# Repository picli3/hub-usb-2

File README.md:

# hub-usb-2

Hub USB 2.0 desarrollado en KiCad, pensado para distribuir conectividad USB desde una placa propia con regulación y protección integradas.

## Propósito del proyecto
Este diseño busca implementar un hub USB reutilizable dentro de un sistema electrónico propio, integrando controlador USB, protección de líneas y regulación de alimentación.

## Qué incluye
- esquemático del hub USB 2.0
- PCB en KiCad
- soporte para alimentación y distribución de múltiples puertos

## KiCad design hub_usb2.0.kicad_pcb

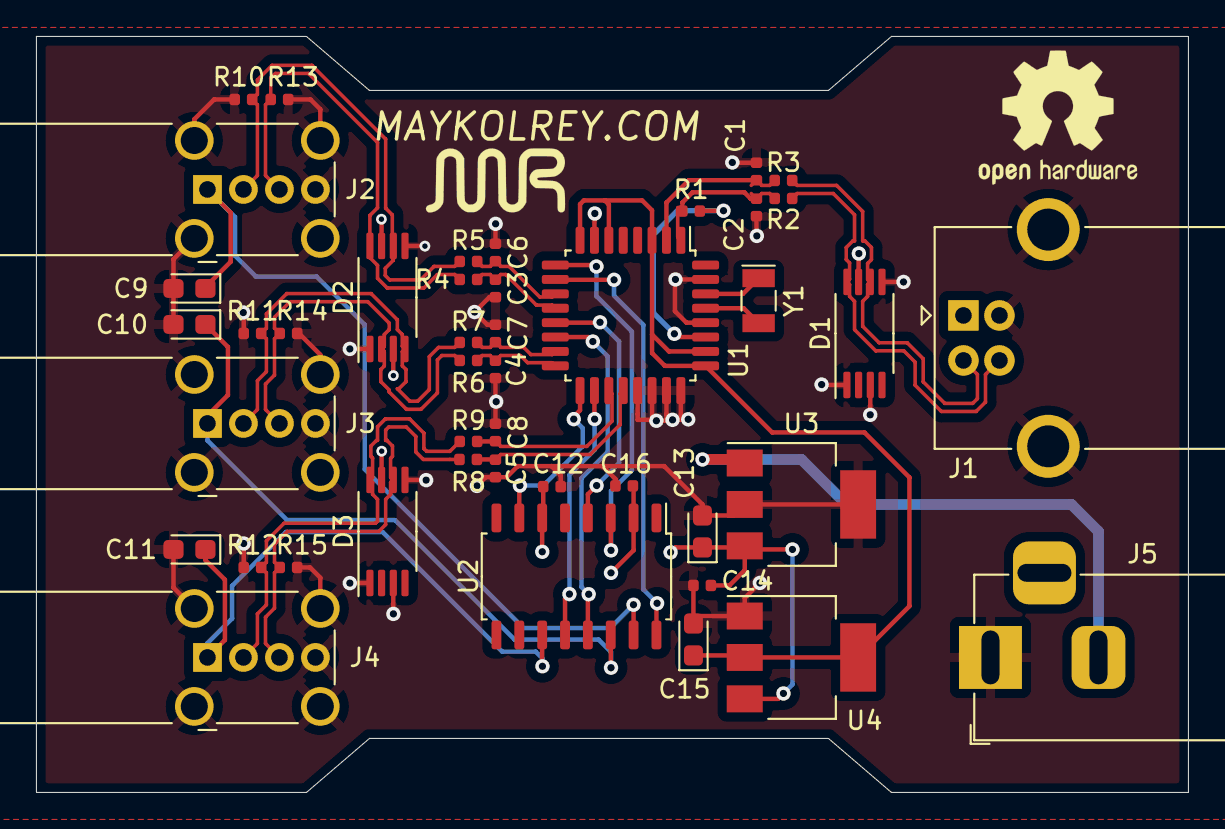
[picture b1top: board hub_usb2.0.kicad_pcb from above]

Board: 4 copper layers, 64.0 x 42.0 mm, 44 parts (0 on the bottom side), 32 nets.

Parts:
C1, C2, C3, C4, C5, C6, C7, C8: 22pF; C_0402_1005Metric
C9, C10, C11: 100uF; CP_EIA-2012-12_Kemet-R
C12, C14, C16: 100nF; C_0402_1005Metric
C13, C15: 4.7uF; CP_EIA-2012-12_Kemet-R
D1, D2, D3: SN75240; TSSOP-8_4.4x3mm_P0.65mm
J1: USB_B; USB_B_OST_USB-B1HSxx_Horizontal
J2, J3, J4: USB_A; USB_A_Wuerth_614004134726_Horizontal
J5: POWER; BarrelJack_Horizontal
R1: 1.5K; R_0402_1005Metric
R2, R3, R4, R5, R6, R7, R8, R9: 27; R_0402_1005Metric
R10, R11, R12, R13, R14, R15: 15K; R_0402_1005Metric
U1: TUSB2036; LQFP-32_7x7mm_P0.8mm
U2: TPS2044; SOIC-16_4.55x10.3mm_P1.27mm
U3: LM7805_TO220; SOT-223-3_TabPin2
U4: LM1117-3.3; SOT-223-3_TabPin2
Y1: 6MHz; Crystal_SMD_MicroCrystal_CC7V-T1A-2Pin_3.2x1.5mm

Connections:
+3V3: C15.1, U1.3, U1.6, U1.8, U1.25, U1.26, U4.2
+5V: C12.1, C13.1, C14.1, C16.1, U2.2, U2.6, U3.3, U4.3
/D0+: C2.1, R1.2, R2.2, U1.1
/D0-: C1.1, R3.2, U1.2
/D1+: C3.1, R4.2, U1.12
/D1-: C6.1, R5.2, U1.11
/D2+: C4.1, R6.2, U1.16
/D2-: C7.1, R7.2, U1.15
/D3+: C5.1, R8.2, U1.20
/D3-: C8.1, R9.2, U1.19
/DC0+: D1.8, J1.3, R2.1
/DC0-: D1.6, J1.2, R3.1
/DC1+: D2.8, J2.3, R4.1, R13.2
/DC1-: D2.6, J2.2, R5.1, R10.2
/DC2+: D2.2, J3.3, R6.1, R14.2
/DC2-: D2.4, J3.2, R7.1, R11.2
/DC3+: D3.6, J4.3, R8.1, R15.2
/DC3-: D3.8, J4.2, R9.1, R12.2
/VBUS1_5V: C9.1, J2.1, U2.15
/VBUS2_5V: C10.1, J3.1, U2.14
/VBUS3_5V: C11.1, J4.1, U2.11
/~EN1: U1.9, U2.3
/~EN2: U1.13, U2.4
/~EN3: U1.17, U2.7
/~OC1: U1.10, U2.16
/~OC2: U1.14, U2.13
/~OC3: U1.18, U2.12
GND: C1.2, C2.2, C3.2, C4.2, C5.2, C6.2, C7.2, C8.2, C9.2, C10.2, C11.2, C12.2, C13.2, C14.2, C15.2, C16.2, D1.1, D1.3, D1.5, D1.7, D2.1, D2.3, D2.5, D2.7, D3.1, D3.3, D3.5, D3.7, J1.4, J1.5, J2.4, J2.5, J3.4, J3.5, J4.4, J4.5, J5.1, R10.1, R11.1, R12.1, R13.1, R14.1, R15.1, U1.7, U1.21, U1.22, U1.23, U1.24, U1.28, U1.31, U3.2, U4.1
unnamed: J5.2, U3.1
unnamed: R1.1, U1.27
unnamed: U1.29, Y1.2
unnamed: U1.30, Y1.1

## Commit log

2022-06-12 version final
2026-04-29 Agrega README con descripción inicial del proyecto
2026-04-29 Mejora README con descripción específica del proyecto
